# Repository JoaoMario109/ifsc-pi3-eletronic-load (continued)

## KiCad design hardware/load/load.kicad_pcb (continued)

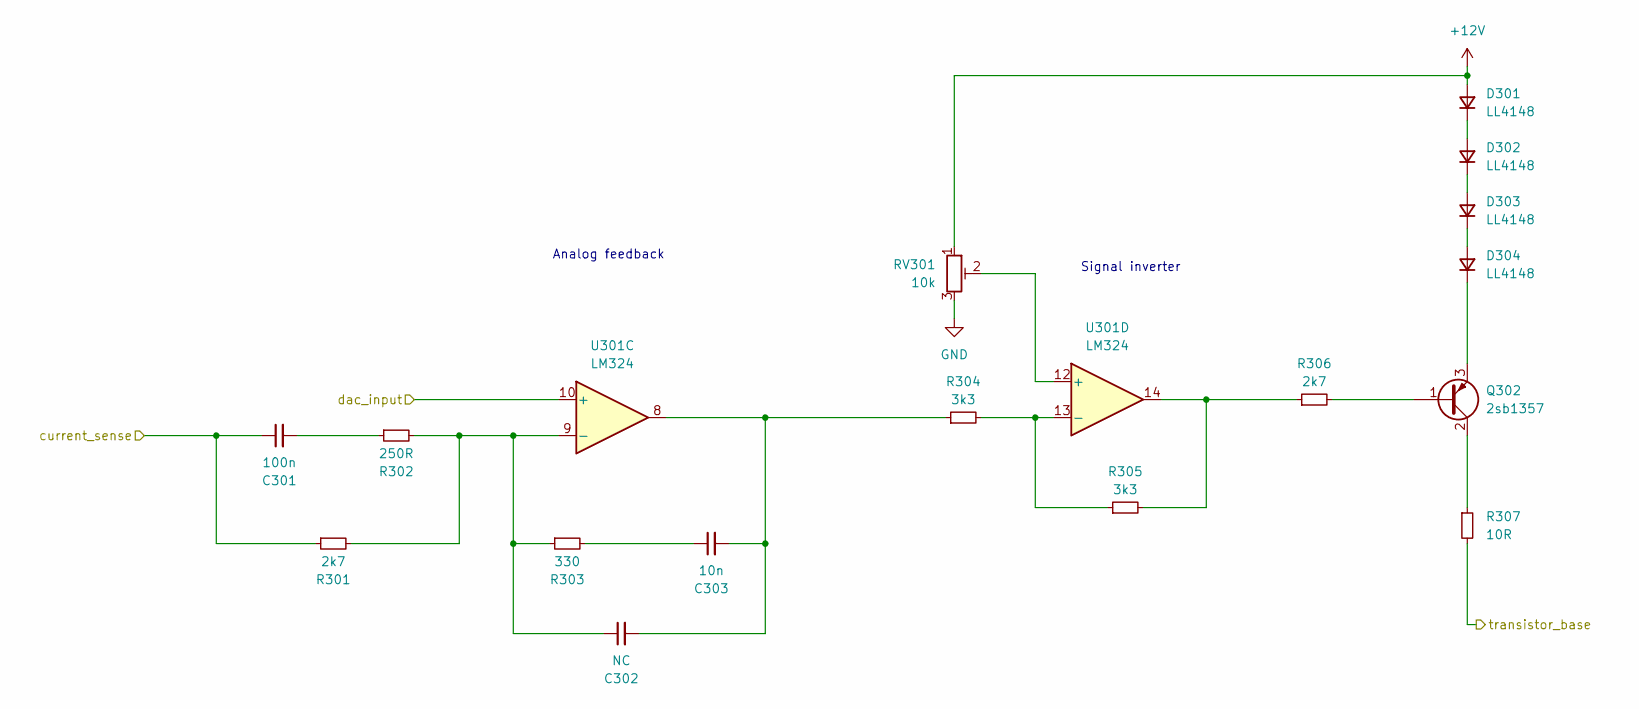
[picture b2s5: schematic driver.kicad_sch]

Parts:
C301: 100n; C_0805_2012Metric_Pad1.18x1.45mm_HandSolder
C302: NC; C_0805_2012Metric_Pad1.18x1.45mm_HandSolder
C303: 10n; C_0805_2012Metric_Pad1.18x1.45mm_HandSolder
D301, D302, D303, D304: LL4148; D_MiniMELF
Q302: 2sb1357; TO-126-3_Vertical
R301, R306: 2k7; R_0805_2012Metric_Pad1.20x1.40mm_HandSolder
R302: 250R; R_0805_2012Metric_Pad1.20x1.40mm_HandSolder
R303: 330; R_0805_2012Metric_Pad1.20x1.40mm_HandSolder
R304, R305: 3k3; R_0805_2012Metric_Pad1.20x1.40mm_HandSolder
R307: 10R; R_0805_2012Metric_Pad1.20x1.40mm_HandSolder
RV301: 10k; Potentiometer_Bourns_3386W_Horizontal
U301: LM324; SOIC-14_3.9x8.7mm_P1.27mm

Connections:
+12V: D301.2 (A), RV301.1; also elsewhere on the board
/analog/Iin_out: C301.1, R301.1; also elsewhere on the board
/analog/dac: U301.10 (+); also elsewhere on the board
/driver/transistor_base: R307.2; also elsewhere on the board
GND: RV301.3; also elsewhere on the board
unnamed: C301.2, R302.1
unnamed: C302.2, C303.2, R304.1, U301.8
unnamed: C303.1, R303.2
unnamed: D301.1 (K), D302.2 (A)
unnamed: D302.1 (K), D303.2 (A)
unnamed: D303.1 (K), D304.2 (A)
unnamed: D304.1 (K), Q302.3 (E)
unnamed: Q302.1 (B), R306.2
unnamed: Q302.2 (C), R307.1
unnamed: R305.2, R306.1, U301.14
unnamed: C302.1, R301.2, R302.2, R303.1, U301.9 (-)
unnamed: RV301.2, U301.12 (+)
unnamed: R304.2, R305.1, U301.13 (-)

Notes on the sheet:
Signal inverter
Analog feedback

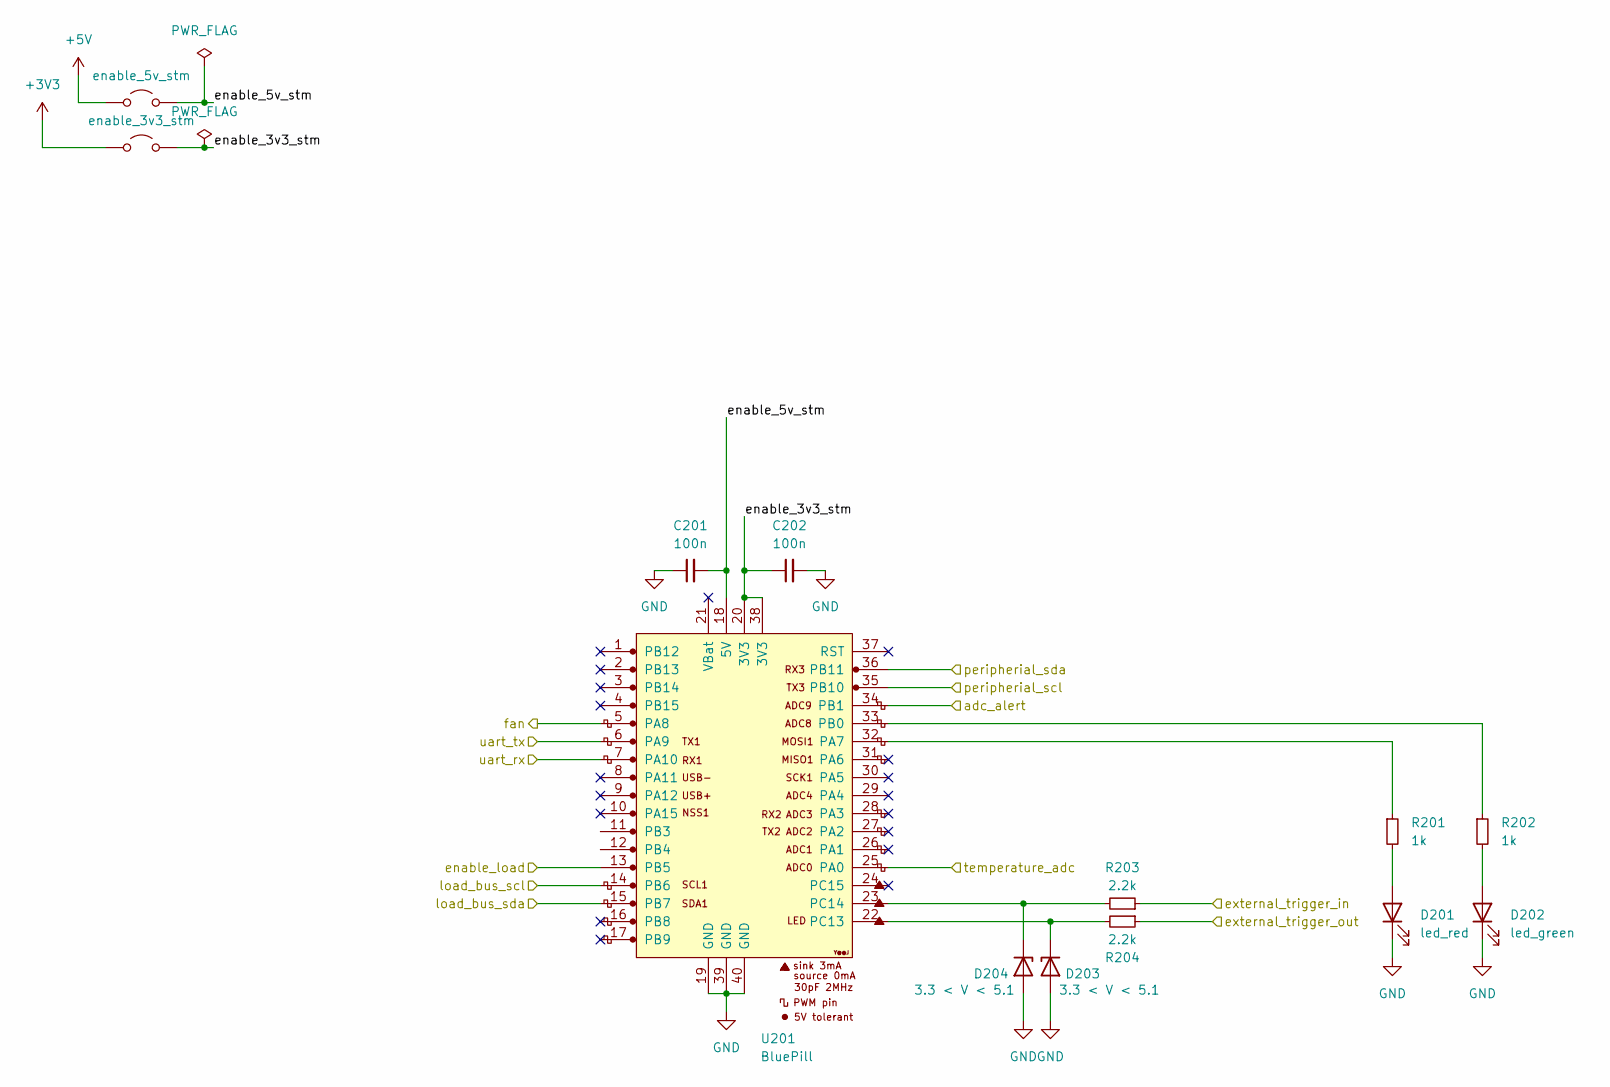
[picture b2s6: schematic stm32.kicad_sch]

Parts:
C201, C202: 100n; C_0805_2012Metric_Pad1.18x1.45mm_HandSolder
D201: led_red; LED_0805_2012Metric_Pad1.15x1.40mm_HandSolder
D202: led_green; LED_0805_2012Metric_Pad1.15x1.40mm_HandSolder
D203, D204: 3.3 < V < 5.1; D_MiniMELF
JP201: enable_5v_stm; SolderJumper-2_P1.3mm_Open_TrianglePad1.0x1.5mm
JP202: enable_3v3_stm; SolderJumper-2_P1.3mm_Open_TrianglePad1.0x1.5mm
R201, R202: 1k; R_0805_2012Metric_Pad1.20x1.40mm_HandSolder
R203, R204: 2.2k; R_0805_2012Metric_Pad1.20x1.40mm_HandSolder
U201: BluePill

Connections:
+3V3: JP202.1 (A); also elsewhere on the board
+5V: JP201.1 (A); also elsewhere on the board
/analog/alert: U201.34 (PB1); also elsewhere on the board
/analog/scl: U201.35 (PB10); also elsewhere on the board
/analog/sda: U201.36 (PB11); also elsewhere on the board
/analog/temperature_adc: U201.25 (PA0); also elsewhere on the board
/stm32/enable_3v3_stm: C202.1, JP202.2 (B), U201.20 (3V3), U201.38 (3V3)
/stm32/enable_5v_stm: C201.2, JP201.2 (B), U201.18 (5V)
/stm32/external_trigger_in: R203.1; also elsewhere on the board
/stm32/external_trigger_out: R204.1; also elsewhere on the board
/stm32/fan: U201.5 (PA8); also elsewhere on the board
/stm32/load_bus_scl: U201.14 (PB6); also elsewhere on the board
/stm32/load_bus_sda: U201.15 (PB7); also elsewhere on the board
/stm32/uart_rx: U201.7 (PA10); also elsewhere on the board
/stm32/uart_tx: U201.6 (PA9); also elsewhere on the board
GND: C201.1, C202.2, D201.1 (K), D202.1 (K), D203.2 (A), D204.2 (A), U201.19 (GND), U201.39 (GND), U201.40 (GND); also elsewhere on the board
unnamed: D201.2 (A), R201.2
unnamed: D202.2 (A), R202.2
unnamed: D203.1 (K), R204.2, U201.22 (PC13)
unnamed: D204.1 (K), R203.2, U201.23 (PC14)
unnamed: R201.1, U201.32 (PA7)
unnamed: R202.1, U201.33 (PB0)

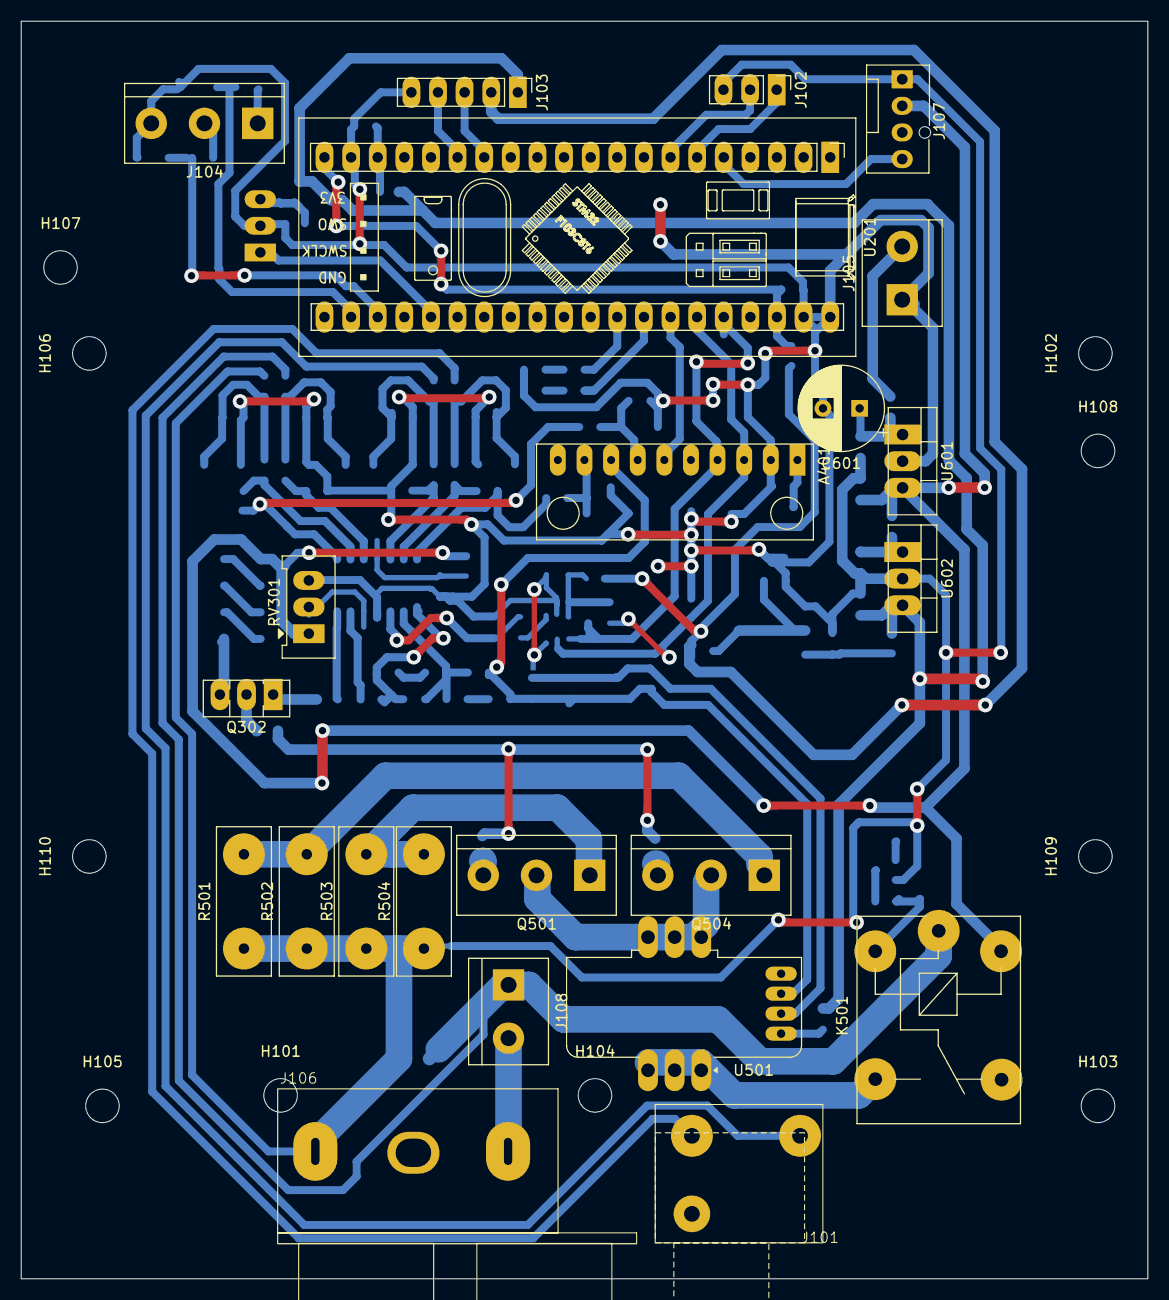
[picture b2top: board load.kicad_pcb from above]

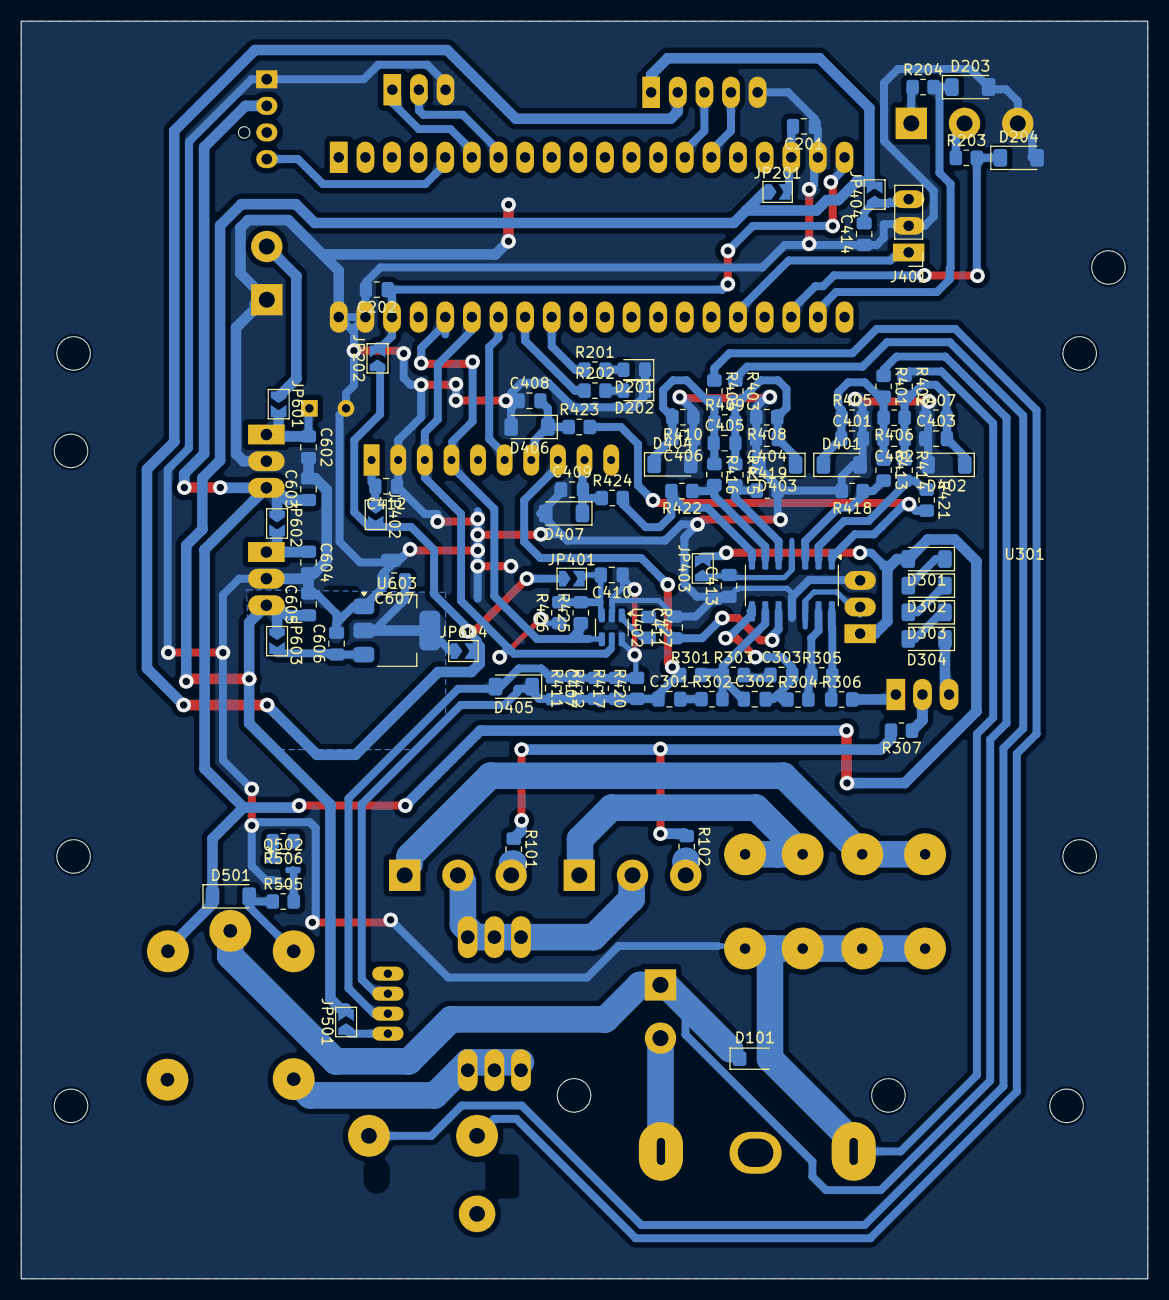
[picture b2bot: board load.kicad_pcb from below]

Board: 2 copper layers, 107.5 x 120.0 mm, 135 parts (102 on the bottom side), 77 nets.

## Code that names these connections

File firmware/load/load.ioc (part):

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Mcu.Name=STM32F103C(8-B)Tx
Mcu.Package=LQFP48
Mcu.UserName=STM32F103C8Tx
PA0-WKUP.Signal=ADCx_IN0
PA13.Mode=Trace_Asynchronous_SW
PA13.Signal=SYS_JTMS-SWDIO
PA14.Mode=Trace_Asynchronous_SW
PA14.Signal=SYS_JTCK-SWCLK
PA7.GPIOParameters=GPIO_Label
PA7.GPIO_Label=LED_RED
PA7.Signal=GPIO_Output
PA8.GPIOParameters=GPIO_Label
PA8.GPIO_Label=FAN
PA8.Signal=S_TIM1_CH1
PB0.GPIOParameters=GPIO_Label
PB0.GPIO_Label=LED_GREEN
PB0.Signal=GPIO_Output
PB1.GPIOParameters=GPIO_Label,GPIO_ModeDefaultEXTI
PB1.GPIO_Label=ADC_ALERT
PB1.GPIO_ModeDefaultEXTI=GPIO_MODE_IT_FALLING
PB1.Signal=GPXTI1
PB10.GPIOParameters=GPIO_Label
PB10.GPIO_Label=PERIPHERIAL_SCL
PB10.Mode=I2C
PB10.Signal=I2C2_SCL
PB11.GPIOParameters=GPIO_Label
PB11.GPIO_Label=PERIPHERIAL_SDA
PB11.Mode=I2C
PB11.Signal=I2C2_SDA
PB15.GPIOParameters=GPIO_Label
PB15.GPIO_Label=ENABLE_LOAD
PB15.Signal=GPIO_Output
PB3.Mode=Trace_Asynchronous_SW
PB3.Signal=SYS_JTDO-TRACESWO
PB6.Mode=Asynchronous
PB6.Signal=USART1_TX
PB7.Mode=Asynchronous
PB7.Signal=USART1_RX
PC13-TAMPER-RTC.GPIOParameters=PinState,GPIO_Label
PC13-TAMPER-RTC.GPIO_Label=EXTERNAL_TRIGGER_OUT
PC13-TAMPER-RTC.PinState=GPIO_PIN_SET
PC13-TAMPER-RTC.Signal=GPIO_Output
PC14-OSC32_IN.GPIOParameters=GPIO_Label
PC14-OSC32_IN.GPIO_Label=EXTERNAL_TRIGGER_IN
PC14-OSC32_IN.Signal=GPIO_Output
PD0-OSC_IN.Mode=HSE-External-Oscillator
PD0-OSC_IN.Signal=RCC_OSC_IN
PD1-OSC_OUT.Mode=HSE-External-Oscillator
PD1-OSC_OUT.Signal=RCC_OSC_OUT
RCC.SYSCLKFreq_VALUE=72000000
RCC.SYSCLKSource=RCC_SYSCLKSOURCE_PLLCLK
board=custom

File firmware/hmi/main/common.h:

#ifndef __COMMON_H__
#define __COMMON_H__

#include <stdbool.h>

/** Hardware Mapping */

/** -- Encoder */
#define GPIO_ENCODER_BTN 33
#define GPIO_ENCODER_DT 25
#define GPIO_ENCODER_CK 26

/** -- Panel Buttons */
#define GPIO_BTN_CC 36
#define GPIO_BTN_CV 39
#define GPIO_BTN_CR 34
#define GPIO_BTN_CP 35

#define GPIO_BTN_EN 2

/** -- LEDs */
#define GPIO_LED_EN 4

/** Communication */

#define GPIO_UART_TX 1
#define GPIO_UART_RX 3

#define GPIO_SPI_MOSI 23
#define GPIO_SPI_MISO 19
#define GPIO_SPI_SCK 18

/** -- SD card */
#define GPIO_SPI_SD_CS 5

/** -- LCD */
#define GPIO_LCD_CS 17
#define GPIO_LCD_DC 15
#define GPIO_LCD_RST 16

#endif /** !__COMMON_H__ */

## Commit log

2024-10-08 .gitignore
    * Add initial gitignore
2024-10-09 README.md
    * Added basic README for project, still raw :)
2024-10-09 docs: Add initial docs resources
2024-10-09 .gitignore: Added zephyr folders on the file
2024-10-09 docs: protocol: Fix set enable/disable in LK and IN
2024-10-09 Firmware: panel: Created first panel poc (hello world)
2024-10-11 README.md: Fixed Contact tab
2024-10-15 .gitignore: Added kicad temp files
2024-10-15 feat(load): Added base schematic and layout
2024-10-15 feat(load): Added kicad components library
2024-10-15 feat(load): Added sensors and control simulation
2024-10-18 panel: cleanup
2024-10-18 hardware: pannel: Added first version of HMI
2024-10-18 feat(load): route logic and optmize layout
2024-10-19 feat(load): finzalize power routing and add mounting holes
2024-10-20 docs: ele-load.drawio: Update general block diagram
    * Updated general block ddiagram of load to reflect better desired
    outcome
2024-10-20 docs: protocol: Small improvements in syntax/spec
2024-10-20 hardware: panel: Small pins and plane adjustments
    * Adjusted pins for sockets to be bigger
    * Regenerated gnp plane
2024-10-20 feat(load): fix DRC errors and warinigs
2024-10-20 hadrware: panel: Rename to Human Machine Interface
2024-10-22 firmware: Add POCs with ESP32 examples for free RTOS
2024-10-22 fix: conect DC pin and change reset to avoid conflicts with UART
2024-10-23 docs: add technical requirements
2024-11-03 feat(load): add load base firmware
2024-11-06 docs: add hardware documentation
2024-11-06 docs: list the data in tables
2024-11-06 Update LICENSE
2024-11-11 feat(load): modify analog PID values on the schematic
2024-11-11 feat(load): modify analog PID values on the simulation
2024-11-11 feat(docs): create docs of analog PID tunning
2024-11-24 feat: add adc auto range and average logic
2024-11-24 feat: add uart parser logic
2024-11-27 feat: configure sensor current constants
2024-11-27 feat(uart): implement rx uart parser
2024-12-04 feat: update uart to use generic parser
2024-12-04 feat(load): add base hmi interface
2024-12-04 docs: update protocol document
2024-12-04 firmware: Add basic HMI
2024-12-04 docs: add ibom load
2024-12-04 feat(load): add constant current control
2024-12-04 feat(load): add constant voltage control
2024-12-04 Update README.md
    clickable LICENSE in readme
2024-12-04 docs: montagem_placa_carga: full report
2024-12-04 hmi: Small fixes on i2c transmission
2024-12-04 feat(load): get i2c buffer via DMA
2024-12-04 docs: update images
2024-12-04 docs: replace images
2025-01-13 WIP firmware
2025-01-13 WIP hardware
2025-02-08 WIP: control
2025-02-11 feat: communicate via uart
2025-02-11 hardware: hmi: Change to UART
2025-02-11 Added server in load
2025-02-12 load: uart comunication wirking
2025-02-12 sdk: create load sdk
2025-02-12 sdk: create ui
2025-02-12 docs: add final assembly and panel assembly docs
2025-02-12 docs: add final assembly images
2025-02-12 load: add small changes
2025-02-12 docs: small changes
2025-02-12 WORKING
2025-02-12 Add base firmware for HMI
